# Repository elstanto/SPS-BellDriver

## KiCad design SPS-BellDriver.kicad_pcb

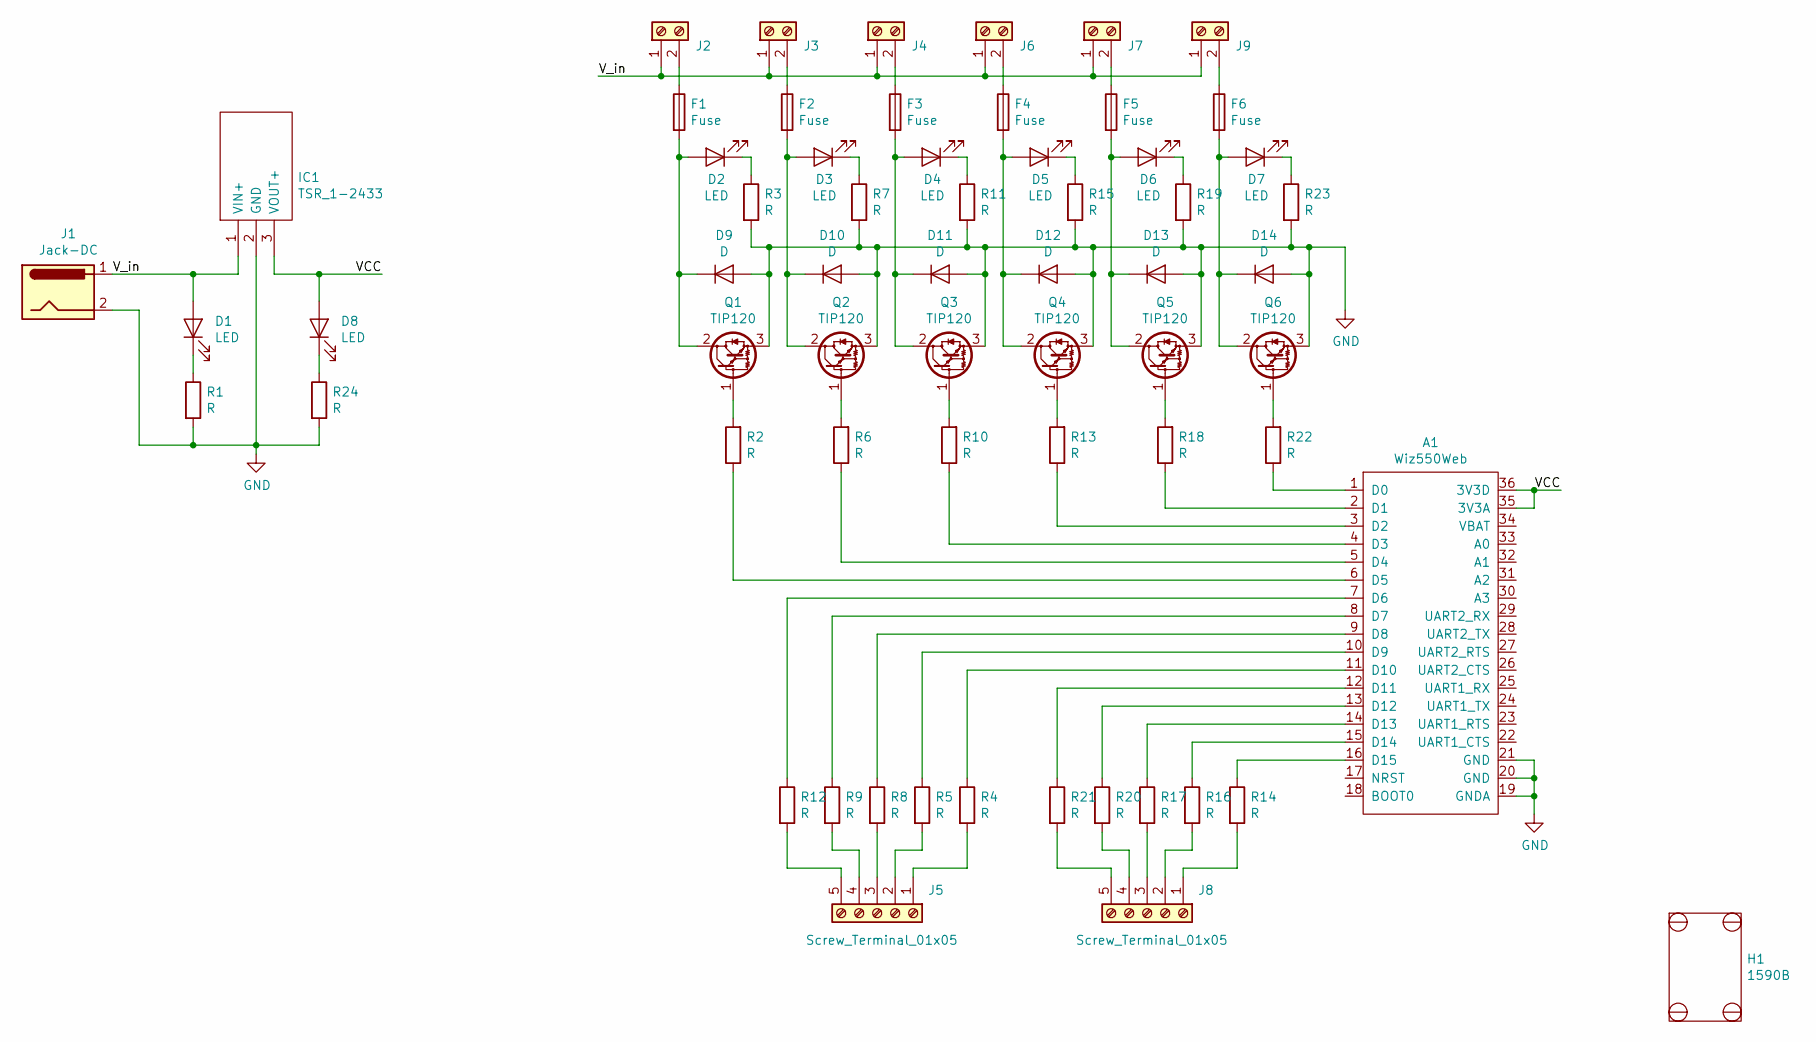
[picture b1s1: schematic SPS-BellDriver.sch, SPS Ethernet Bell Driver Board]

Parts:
A1: Wiz550Web
D1, D8: LED; LED_D3.0mm
D2, D3, D4, D5, D6, D7: LED; LED_D3.0mm_Horizontal_O1.27mm_Z2.0mm
D9, D10, D11, D12, D13, D14: D; D_DO-41_SOD81_P7.62mm_Horizontal
F1, F2, F3, F4, F5, F6: Fuse; RXEF0172
H1: 1590B
IC1: TSR_1-2433; TSR-1-2433; Manufacturer_Part_Number TSR 1-2433
J1: Jack-DC; BarrelJack_Horizontal
J2, J3, J4, J6, J7, J9: Screw_Terminal_01x02; PhoenixContact_MSTBA_2,5_2-G_1x02_P5.00mm_Horizontal
J5, J8: Screw_Terminal_01x05; SHDR5W100P0X350_1X5_1890X920X725P
Q1, Q2, Q3, Q4, Q5, Q6: TIP120; TO-220-3_Vertical
R1, R2, R3, R4, R5, R6, R7, R8, R9, R10, R11, R12, R13, R14, R15, R16, R17, R18, R19, R20, R21, R22, R23: R; R_Axial_DIN0207_L6.3mm_D2.5mm_P2.54mm_Vertical
R24: R; R_Axial_DIN0207_L6.3mm_D2.5mm_P5.08mm_Vertical

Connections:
/VCC: A1.35 (3V3A), A1.36 (3V3D), D8.2 (A), IC1.3 (VOUT+)
/V_in: D1.2 (A), IC1.1 (VIN+), J1.1, J2.1, J3.1, J4.1, J6.1, J7.1, J9.1
GND: A1.19 (GNDA), A1.20 (GND), A1.21 (GND), D9.2 (A), D10.2 (A), D11.2 (A), D12.2 (A), D13.2 (A), D14.2 (A), IC1.2 (GND), J1.2, Q1.3 (E), Q2.3 (E), Q3.3 (E), Q4.3 (E), Q5.3 (E), Q6.3 (E), R1.2, R3.2, R7.2, R11.2, R15.2, R19.2, R23.2, R24.2
unnamed: A1.1 (D0), R22.1
unnamed: A1.2 (D1), R18.1
unnamed: A1.3 (D2), R13.1
unnamed: A1.4 (D3), R10.1
unnamed: A1.5 (D4), R6.1
unnamed: A1.6 (D5), R2.1
unnamed: A1.7 (D6), R12.1
unnamed: A1.8 (D7), R9.1
unnamed: A1.9 (D8), R8.1
unnamed: A1.10 (D9), R5.1
unnamed: A1.11 (D10), R4.1
unnamed: A1.12 (D11), R21.1
unnamed: A1.13 (D12), R20.1
unnamed: A1.14 (D13), R17.1
unnamed: A1.15 (D14), R16.1
unnamed: A1.16 (D15), R14.1
unnamed: D1.1 (K), R1.1
unnamed: D2.1 (K), R3.1
unnamed: D2.2 (A), D9.1 (K), F1.2, Q1.2 (C)
unnamed: D3.1 (K), R7.1
unnamed: D4.1 (K), R11.1
unnamed: D5.1 (K), R15.1
unnamed: D6.1 (K), R19.1
unnamed: D7.1 (K), R23.1
unnamed: D8.1 (K), R24.1
unnamed: D3.2 (A), D10.1 (K), F2.2, Q2.2 (C)
unnamed: D4.2 (A), D11.1 (K), F3.2, Q3.2 (C)
unnamed: D5.2 (A), D12.1 (K), F4.2, Q4.2 (C)
unnamed: D6.2 (A), D13.1 (K), F5.2, Q5.2 (C)
unnamed: D7.2 (A), D14.1 (K), F6.2, Q6.2 (C)
unnamed: F1.1, J2.2
unnamed: F2.1, J3.2
unnamed: F3.1, J4.2
unnamed: F4.1, J6.2
unnamed: F5.1, J7.2
unnamed: F6.1, J9.2
unnamed: J5.1, R4.2
unnamed: J5.2, R5.2
unnamed: J5.3, R8.2
unnamed: J5.4, R9.2
unnamed: J5.5, R12.2
unnamed: J8.1, R14.2
unnamed: J8.2, R16.2
unnamed: J8.3, R17.2
unnamed: J8.4, R20.2
unnamed: J8.5, R21.2
unnamed: Q1.1 (B), R2.2
unnamed: Q2.1 (B), R6.2
unnamed: Q3.1 (B), R10.2
unnamed: Q4.1 (B), R13.2
unnamed: Q5.1 (B), R18.2
unnamed: Q6.1 (B), R22.2

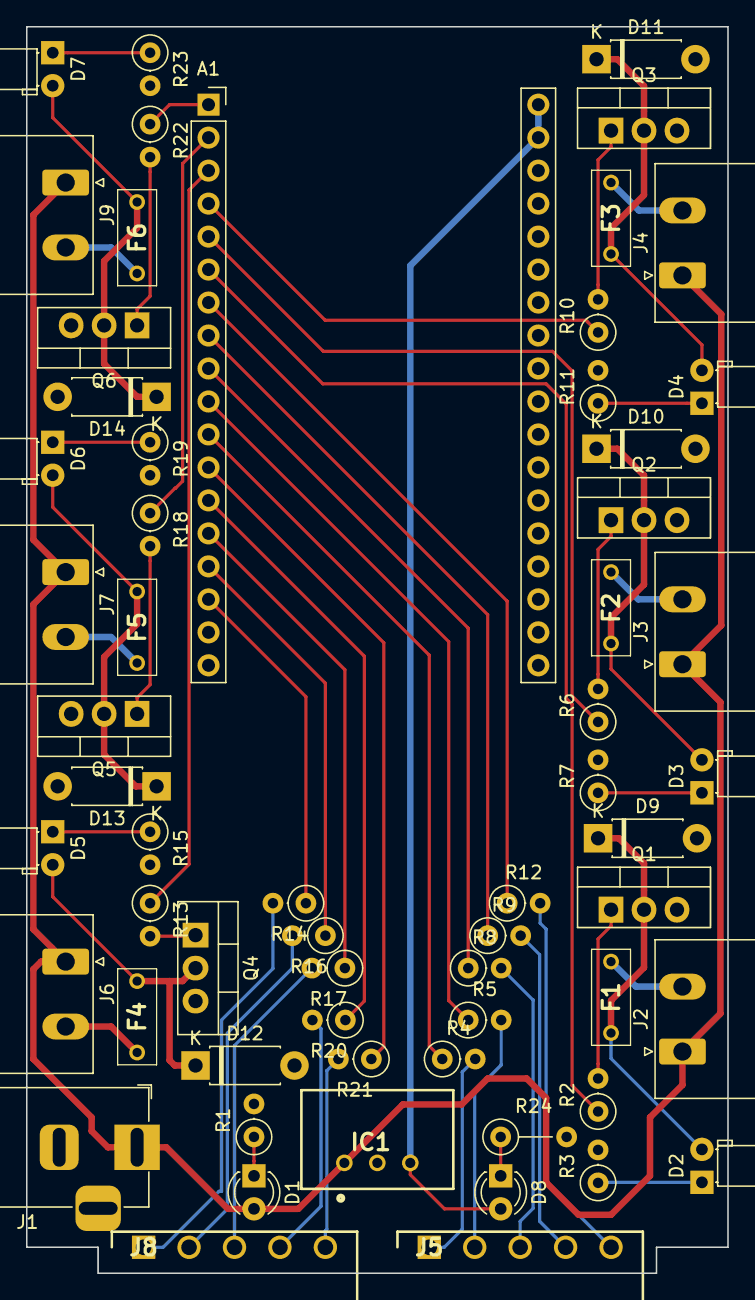
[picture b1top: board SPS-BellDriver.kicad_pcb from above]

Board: 2 copper layers, 54.0 x 96.0 mm, 62 parts (0 on the bottom side), 55 nets.

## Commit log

2020-02-21 Initial commit. Schematic mostly complete.
